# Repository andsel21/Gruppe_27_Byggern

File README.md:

# Gruppe_27_Byggern
TTK4155 - Embedded Pong  Lab 

TODO:

PD5 - clock signal til ADC. software må settes opp.

Her kan vi lage til README-info som nødvendig info for prosjektet  

UART - UCSRA - STATUS REGISTER
			BIT7 - RECEIVE COMPLETE - data er mottatt
			BIT6 - TRANSMIT COMPLETE - hele sendingen er ferdig
			BIT5 - DATA REGISTER EMPTY - UDR0 er klar for neste byte
			BIT4 - FRAME ERROR
			BIT3 - DATA OVERRUN
			BIT2 - PARITY ERROR
			BIT1 - Double the USART Transmission Speed
			BIT0 - MULTI-PROCESSOR COMMUNICATION MODE

UART - UCSRB - CONTROL REGISTER
			BIT7 - RX COMPLETE INTERRUPT ENABLE - interrupt når en byte er mottatt
			BIT6 - TX COMPLETE INTERRUPT ENABLE - interrupt når en hel UART-frame er ferdig sendt
			BIT5 - USART DATA REGISTER EMPTY INTERRUPT ENABLE - interrupt når UDR er ledig for neste byte
			BIT4 - RXEN: RECEIVER ENABLE
			BIT3 - TXEN: TRANSMIT ENABLE
			BIT2 - UCSZ2: CHARACTER SIZE - Brukes sammen med UCSZ1:0 for å velge antall databits
			BIT1 - RXB8: RECEIVE DATA BIT 8 - 9. mottatte databit ved 9-bit UART
			BIT0 - TXB8: TRANSMIT DATA BIT 8 - 9. databit som skal sendes ved 9-bit UART
			
UART - USCRC - Configuration / Frame Format
			BIT7 - URSEL - REGISTER SELECT
			BIT6 - UMSEL - USART MODE SELECT
			BIT5 - PARITY MODE BIT 1
			BIT4 - PARITY MODE BIT 0
			BIT3 - USBS - STOP BIT SELECT - 1 ELLER 2 STOPBITS
			BIT2 - UCSZ1 - CHARACTER SIZE BIT 1
			BIT1 - UCSZ2 - CHARACTER SIZE BIT 0
			BIT0 - UCPOL - CLOCK POLARITY - brukes ved synkron USART

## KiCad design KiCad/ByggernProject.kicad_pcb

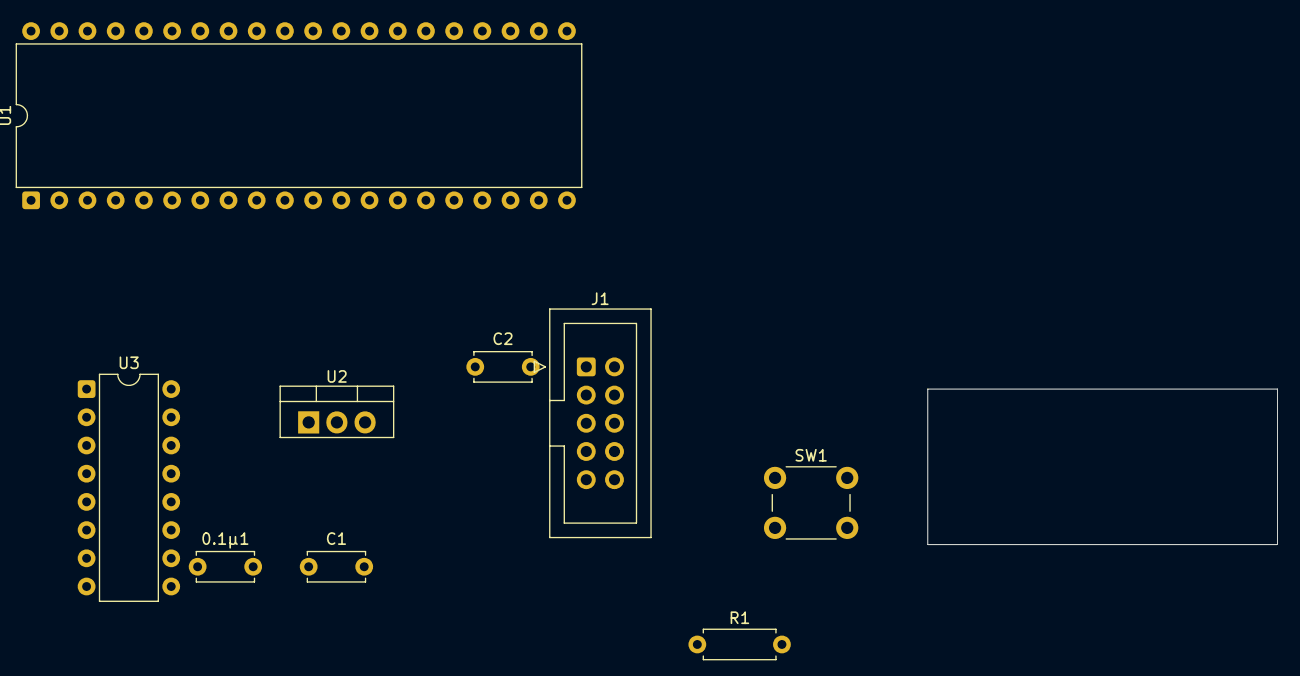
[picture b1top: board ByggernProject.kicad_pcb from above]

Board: 2 copper layers, 31.5 x 14.0 mm, 9 parts (0 on the bottom side), 11 nets, no tracks yet.

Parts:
0.1µ1: C; C_Disc_D5.0mm_W2.5mm_P5.00mm
C1, C2: C; C_Disc_D5.0mm_W2.5mm_P5.00mm
J1: AVR-JTAG-10; IDC-Header_2x05_P2.54mm_Vertical
R1: 10kΩ; R_Axial_DIN0207_L6.3mm_D2.5mm_P7.62mm_Horizontal
SW1: SW_Push; SW_PUSH_6mm
U1: ATmega16-16P; DIP-40_W15.24mm
U2: L7805; TO-220-3_Vertical
U3: MAX232; DIP-16_W7.62mm

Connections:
+10.2V: C1.1, U2.1 (IN)
/+5V: C2.1, J1.4 (VREF), U1.10 (VCC), U2.3 (OUT)
/DXD0: J1.9 (TDI), U1.29 (PC7)
GND: C1.2, C2.2, J1.2 (GND), J1.10 (GND), SW1.2, U2.2 (GND)
unnamed: J1.1 (TCK), U1.26 (PC4)
unnamed: J1.3 (TDO), U1.28 (PC6)
unnamed: J1.5 (TMS), U1.27 (PC5)
unnamed: U1.11 (GND), U1.31 (GND)
unnamed: U1.14 (PD0), U3.11 (T1IN)
unnamed: U1.15 (PD1), U3.12 (R1OUT)
unnamed: 0.1µ1.2, R1.2, SW1.1, U1.9 (~RESET), U3.9 (R2OUT)
